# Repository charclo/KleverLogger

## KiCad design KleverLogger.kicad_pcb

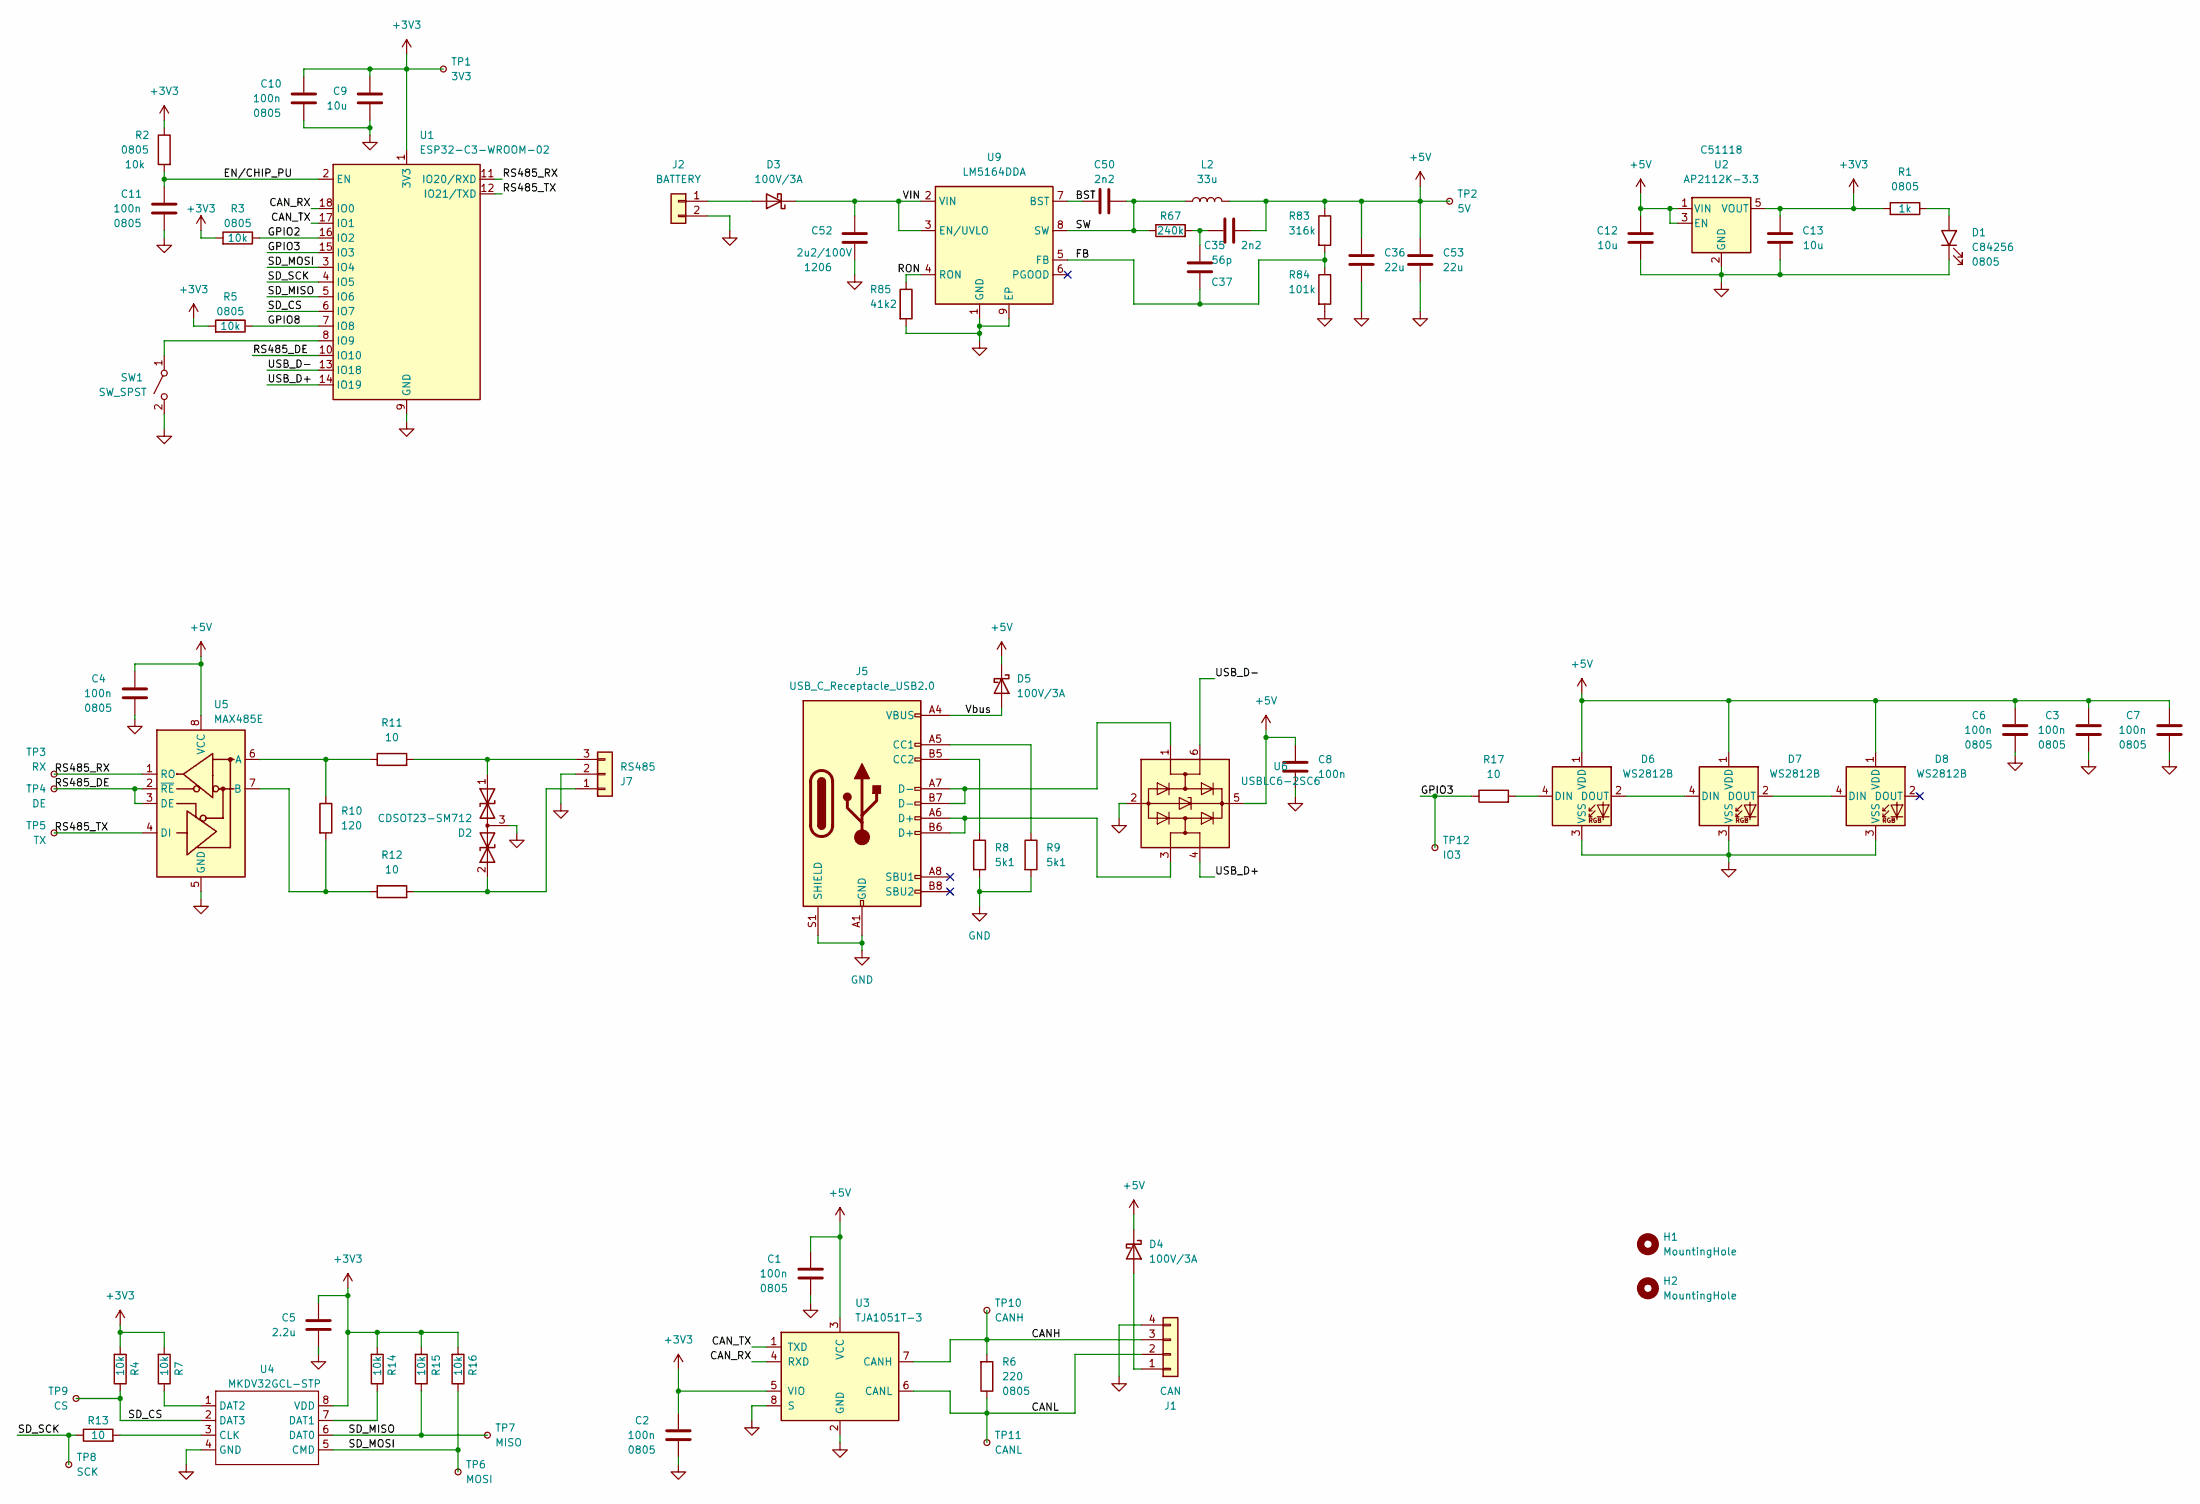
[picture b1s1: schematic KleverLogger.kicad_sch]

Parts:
C1, C2, C3, C4, C6, C7, C8, C10, C11: 100n; C_0805_2012Metric; LCSC C49678
C5: 2.2u; C_0805_2012Metric; LCSC C377773
C9, C12, C13: 10u; C_0805_2012Metric; LCSC C15850
C35, C50: 2n2; C_0805_2012Metric; LCSC C28260
C36, C53: 22u; C_0805_2012Metric; LCSC C45783
C37: 56p; C_0805_2012Metric
C52: 2u2/100V; C_1206_3216Metric; LCSC C577211
D1: LED_0805_2012Metric; LCSC C84256
D2: CDSOT23-SM712; TSOT-23; LCSC C5122012
D3, D4, D5: 100V/3A; D_SOD-123F; LCSC C106914
D6, D7, D8: WS2812B; LED_WS2812B_PLCC4_5.0x5.0mm_P3.2mm; LCSC C2843785
H1, H2: MountingHole; MountingHole_3.2mm_M3
J1: CAN; JST_PH_S4B-PH-K_1x04_P2.00mm_Horizontal
J2: BATTERY; JST_PH_S2B-PH-K_1x02_P2.00mm_Horizontal
J5: USB_C_Receptacle_USB2.0; USB_C_Receptacle_HRO_TYPE-C-31-M-12
J7: RS485; JST_PH_S3B-PH-K_1x03_P2.00mm_Horizontal
L2: 33u; L_Taiyo-Yuden_NR-80xx
R1: 1k; R_0805_2012Metric; LCSC C17513
R2, R3, R4, R5, R7, R14, R15, R16: 10k; R_0805_2012Metric; LCSC C17414
R6: 220; R_0805_2012Metric; LCSC C17557
R8, R9: 5k1; R_0805_2012Metric; LCSC C27834
R10: 120; R_0805_2012Metric; LCSC C17437
R11, R12, R13, R17: 10; R_0805_2012Metric; LCSC C17415
R67: 240k; R_0805_2012Metric
R83: 316k; R_0805_2012Metric
R84: 101k; R_0805_2012Metric
R85: 41k2; R_0805_2012Metric; LCSC C149504
SW1: SW_SPST; Flat_SMD_Switch; LCSC C318884
TP1: 3V3; TestPoint_Pad_D0.8mm
TP2: 5V; TestPoint_Pad_D0.8mm
TP3: RX; TestPoint_Pad_D0.8mm
TP4: DE; TestPoint_Pad_D0.8mm
TP5: TX; TestPoint_Pad_D0.8mm
TP6: MOSI; TestPoint_Pad_D0.8mm
TP7: MISO; TestPoint_Pad_D0.8mm
TP8: SCK; TestPoint_Pad_D0.8mm
TP9: CS; TestPoint_Pad_D0.8mm
TP10: CANH; TestPoint_Pad_D0.8mm
TP11: CANL; TestPoint_Pad_D0.8mm
TP12: IO3; TestPoint_Pad_D0.8mm
U1: ESP32-C3-WROOM-02
U2: AP2112K-3.3; SOT-23-5; LCSC C51118
U3: TJA1051T-3; SOIC-8_3.9x4.9mm_P1.27mm; LCSC C58988
U4: MKDV32GCL-STP; Manufacturer Part MKDV32GCL-STP; LCSC Part Name 32Gb SD NAND 商业级 SDNAND 升级款
U5: MAX485E; SOIC-8_3.9x4.9mm_P1.27mm
U6: USBLC6-2SC6; SOT-23-6; LCSC C2827654
U9: LM5164DDA; HSOP-8-1EP_3.9x4.9mm_P1.27mm_EP2.41x3.1mm_ThermalVias; LCSC C477928

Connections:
+3V3: C2.1, C5.1, C9.1, C10.1, C13.1, R1.1, R2.2, R3.1, R4.1, R5.1, R7.1, R14.1, R15.1, R16.1, TP1.1, U1.1 (3V3), U2.5 (VOUT), U3.5 (VIO), U4.8 (VDD)
+5V: C1.1, C3.1, C4.1, C6.1, C7.1, C8.1, C12.1, C35.2, C36.1, C53.1, D4.1 (K), D5.1 (K), D6.1 (VDD), D7.1 (VDD), D8.1 (VDD), L2.2, R83.1, TP2.1, U2.1 (VIN), U2.3 (EN), U3.3 (VCC), U5.8 (VCC), U6.5 (VBUS)
/BST: C50.2, U9.7 (BST)
/CANH: J1.3, R6.1, TP10.1, U3.7 (CANH)
/CANL: J1.2, R6.2, TP11.1, U3.6 (CANL)
/CAN_RX: U1.18 (IO0), U3.4 (RXD)
/CAN_TX: U1.17 (IO1), U3.1 (TXD)
/EN/CHIP_PU: C11.1, R2.1, U1.2 (EN)
/FB: C37.1, R83.2, R84.1, U9.5 (FB)
/GPIO2: R3.2, U1.16 (IO2)
/GPIO3: R17.1, TP12.1, U1.15 (IO3)
/GPIO8: R5.2, U1.7 (IO8)
/RON: R85.1, U9.4 (RON)
/RS485_DE: TP4.1, U1.10 (IO10), U5.2 (~RE), U5.3 (DE)
/RS485_RX: TP3.1, U1.11 (IO20/RXD), U5.1 (RO)
/RS485_TX: TP5.1, U1.12 (IO21/TXD), U5.4 (DI)
/SD_CS: R4.2, TP9.1, U1.6 (IO7), U4.2 (DAT3)
/SD_MISO: R15.2, TP7.1, U1.5 (IO6), U4.6 (DAT0)
/SD_MOSI: R16.2, TP6.1, U1.3 (IO4), U4.5 (CMD)
/SD_SCK: R13.1, TP8.1, U1.4 (IO5)
/SW: C50.1, L2.1, R67.1, U9.8 (SW)
/USB_D+: U1.14 (IO19), U6.4 (I/O2)
/USB_D-: U1.13 (IO18), U6.6 (I/O1)
/VIN: C52.1, D3.1 (K), U9.2 (VIN), U9.3 (EN/UVLO)
/Vbus: D5.2 (A), J5.A4 (VBUS), J5.A9 (VBUS), J5.B4 (VBUS), J5.B9 (VBUS)
GND: C1.2, C2.2, C3.2, C4.2, C5.2, C6.2, C7.2, C8.2, C9.2, C10.2, C11.2, C12.2, C13.2, C36.2, C52.2, C53.2, D1.1 (K), D2.3 (common), D6.3 (VSS), D7.3 (VSS), D8.3 (VSS), J1.4, J2.2, J5.A1 (GND), J5.A12 (GND), J5.B1 (GND), J5.B12 (GND), J5.S1 (SHIELD), J7.2, R8.2, R9.2, R84.2, R85.2, SW1.2 (B), U1.9 (GND), U1.19 (GND), U2.2 (GND), U3.2 (GND), U3.8 (S), U4.4 (GND), U5.5 (GND), U6.2 (GND), U9.1 (GND), U9.9 (EP)
unnamed: C35.1, C37.2, R67.2
unnamed: D1.2 (A), R1.2
unnamed: D2.1 (A1), J7.3, R11.2
unnamed: D2.2 (A2), J7.1, R12.2
unnamed: D3.2 (A), J2.1
unnamed: D4.2 (A), J1.1
unnamed: D6.4 (DIN), R17.2
unnamed: D6.2 (DOUT), D7.4 (DIN)
unnamed: D7.2 (DOUT), D8.4 (DIN)
unnamed: J5.A5 (CC1), R9.1
unnamed: J5.B5 (CC2), R8.1
unnamed: J5.A6 (D+), J5.B6 (D+), U6.3 (I/O2)
unnamed: J5.A7 (D-), J5.B7 (D-), U6.1 (I/O1)
unnamed: SW1.1 (A), U1.8 (IO9)
unnamed: R13.2, U4.3 (CLK)
unnamed: R14.2, U4.7 (DAT1)
unnamed: R7.2, U4.1 (DAT2)
unnamed: R10.1, R11.1, U5.6 (A)
unnamed: R10.2, R12.1, U5.7 (B)

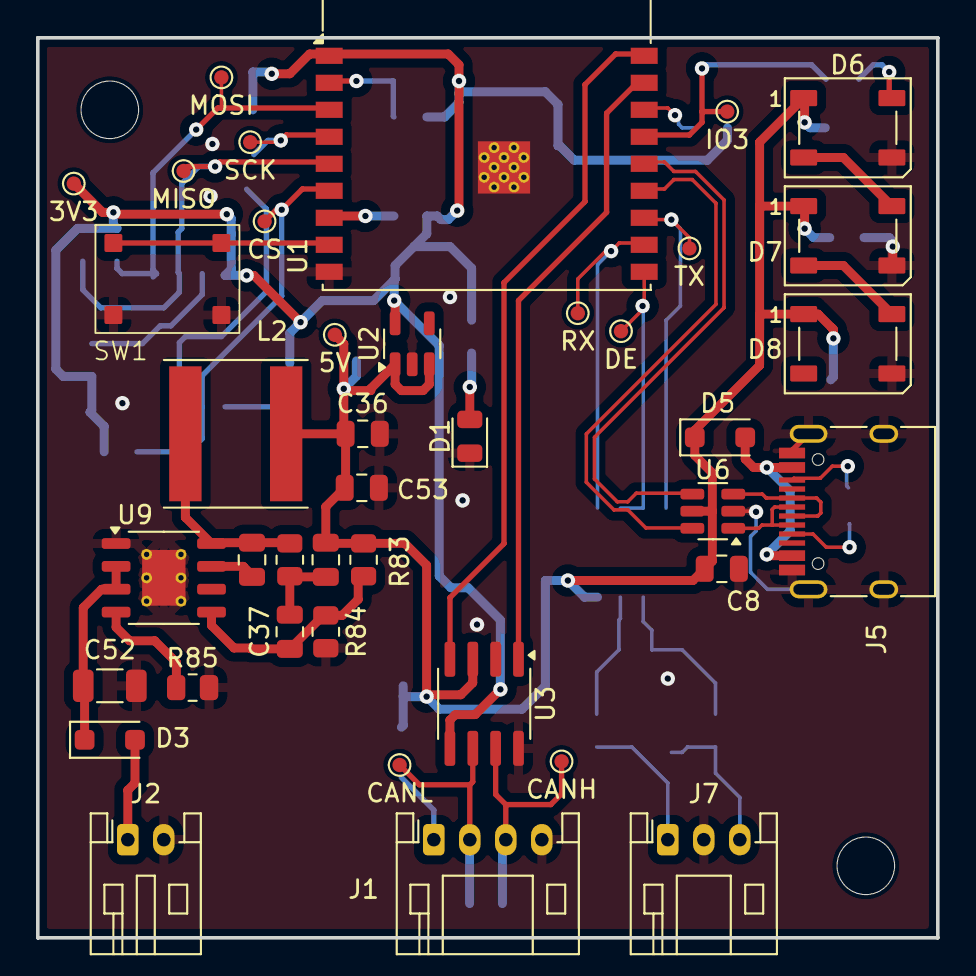
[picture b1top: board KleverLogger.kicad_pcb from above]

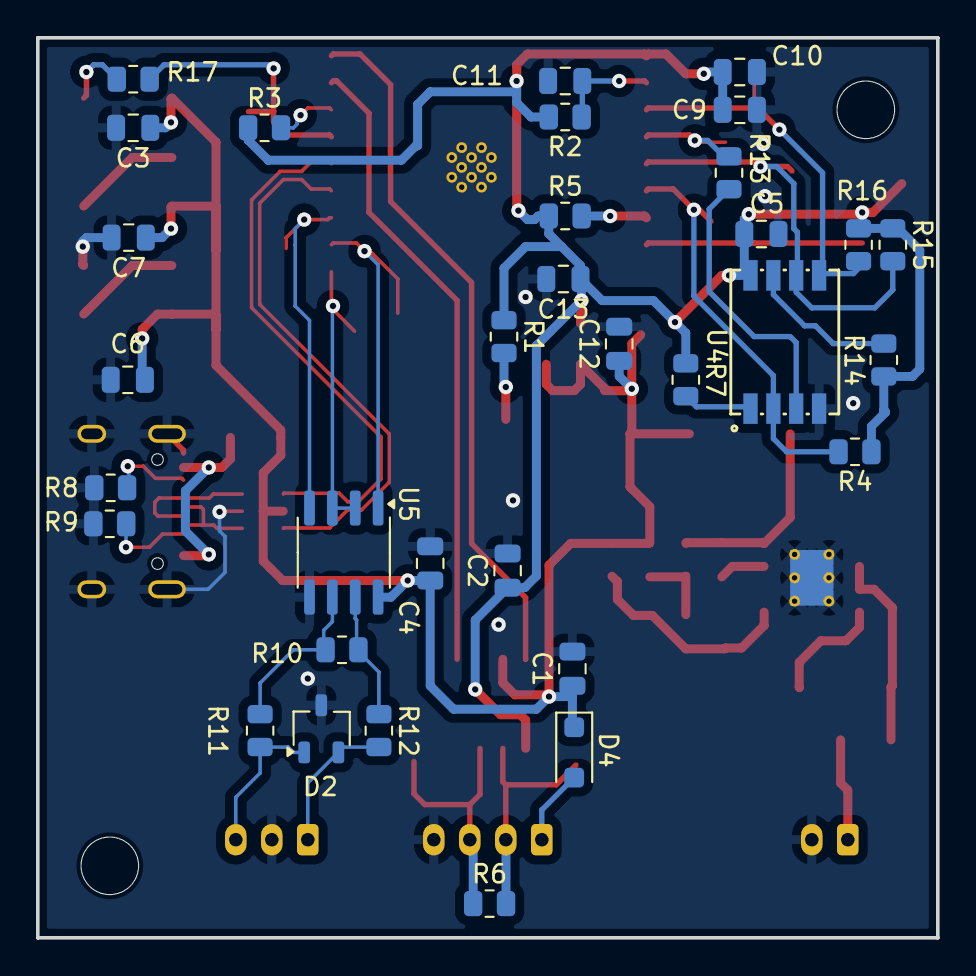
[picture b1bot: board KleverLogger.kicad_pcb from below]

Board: 4 copper layers, 50.0 x 50.0 mm, 75 parts (33 on the bottom side), 45 nets.

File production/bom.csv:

Designator,Footprint,Quantity,Value,LCSC Part #
"C1, C10, C11, C2, C3, C4, C6, C7, C8",0805,9,100n,C49678
"C12, C13, C9",0805,3,10u,C15850
"C35, C50",0805,2,2n2,C28260
"C36, C53",0805,2,22u,C45783
C37,0805,1,56p,
C5,0805,1,2.2u,C377773
C52,1206,1,2u2/100V,C577211
D1,0805,1,~,C84256
D2,TSOT-23,1,CDSOT23-SM712,C5122012
"D3, D4, D5",D_SOD-123F,3,100V/3A,C106914
"D6, D7, D8",LED_WS2812B_PLCC4_5.0x5.0mm_P3.2mm,3,WS2812B,C2843785
"H1, H2",MountingHole_3.2mm_M3,2,MountingHole,
J1,JST_PH_S4B-PH-K_1x04_P2.00mm_Horizontal,1,CAN,
J2,JST_PH_S2B-PH-K_1x02_P2.00mm_Horizontal,1,BATTERY,
J5,USB_C_Receptacle_HRO_TYPE-C-31-M-12,1,USB_C_Receptacle_USB2.0,
J7,JST_PH_S3B-PH-K_1x03_P2.00mm_Horizontal,1,RS485,
L2,L_Taiyo-Yuden_NR-80xx,1,33u,
R1,0805,1,1k,C17513
R10,0805,1,120,C17437
"R11, R12, R13, R17",0805,4,10,C17415
"R14, R15, R16, R2, R3, R4, R5, R7",0805,8,10k,C17414
R6,0805,1,220,C17557
R67,0805,1,240k,
"R8, R9",0805,2,5k1, C27834
R83,0805,1,316k,
R84,0805,1,101k,
R85,0805,1,41k2,C149504
SW1,Flat_SMD_Switch,1,SW_SPST,C318884
TP1,TestPoint_Pad_D0.8mm,1,3V3,
TP10,TestPoint_Pad_D0.8mm,1,CANH,
TP11,TestPoint_Pad_D0.8mm,1,CANL,
TP12,TestPoint_Pad_D0.8mm,1,IO3,
TP2,TestPoint_Pad_D0.8mm,1,5V,
TP3,TestPoint_Pad_D0.8mm,1,RX,
TP4,TestPoint_Pad_D0.8mm,1,DE,
TP5,TestPoint_Pad_D0.8mm,1,TX,
TP6,TestPoint_Pad_D0.8mm,1,MOSI,
TP7,TestPoint_Pad_D0.8mm,1,MISO,
TP8,TestPoint_Pad_D0.8mm,1,SCK,
TP9,TestPoint_Pad_D0.8mm,1,CS,
U1,ESP32-C3-WROOM-02,1,ESP32-C3-WROOM-02,
U2,SOT-23-5,1,AP2112K-3.3,C51118
U3,SOIC-8_3.9x4.9mm_P1.27mm,1,TJA1051T-3,C58988
U4,MKDV32GCL-STP,1,~,
U5,SOIC-8_3.9x4.9mm_P1.27mm,1,MAX485E,
U6,SOT-23-6,1,USBLC6-2SC6,C2827654
U9,HSOP-8-1EP_3.9x4.9mm_P1.27mm_EP2.41x3.1mm_ThermalVias,1,LM5164DDA,C477928

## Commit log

2025-09-26 USB updates
2025-09-27 Update to components
2025-10-15 After ordering v0.1
